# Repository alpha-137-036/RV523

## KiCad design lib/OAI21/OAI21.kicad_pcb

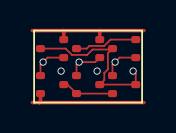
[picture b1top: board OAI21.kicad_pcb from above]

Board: 2 copper layers, 6 parts (0 on the bottom side), 7 nets.

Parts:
N1, N2, N3: NMOS; SOT523
P1, P2, P3: PMOS; SOT523

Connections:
A: N1.1 (G), P1.1 (G)
B1: N2.1 (G), P2.1 (G)
B2: N3.1 (G), P3.1 (G)
VDD: P1.2 (S), P2.2 (S)
Y: N2.3 (D), N3.3 (D), P1.3 (D), P3.3 (D)
intB: P2.3 (D), P3.2 (S)
intN: N1.3 (D), N2.2 (S), N3.2 (S)
